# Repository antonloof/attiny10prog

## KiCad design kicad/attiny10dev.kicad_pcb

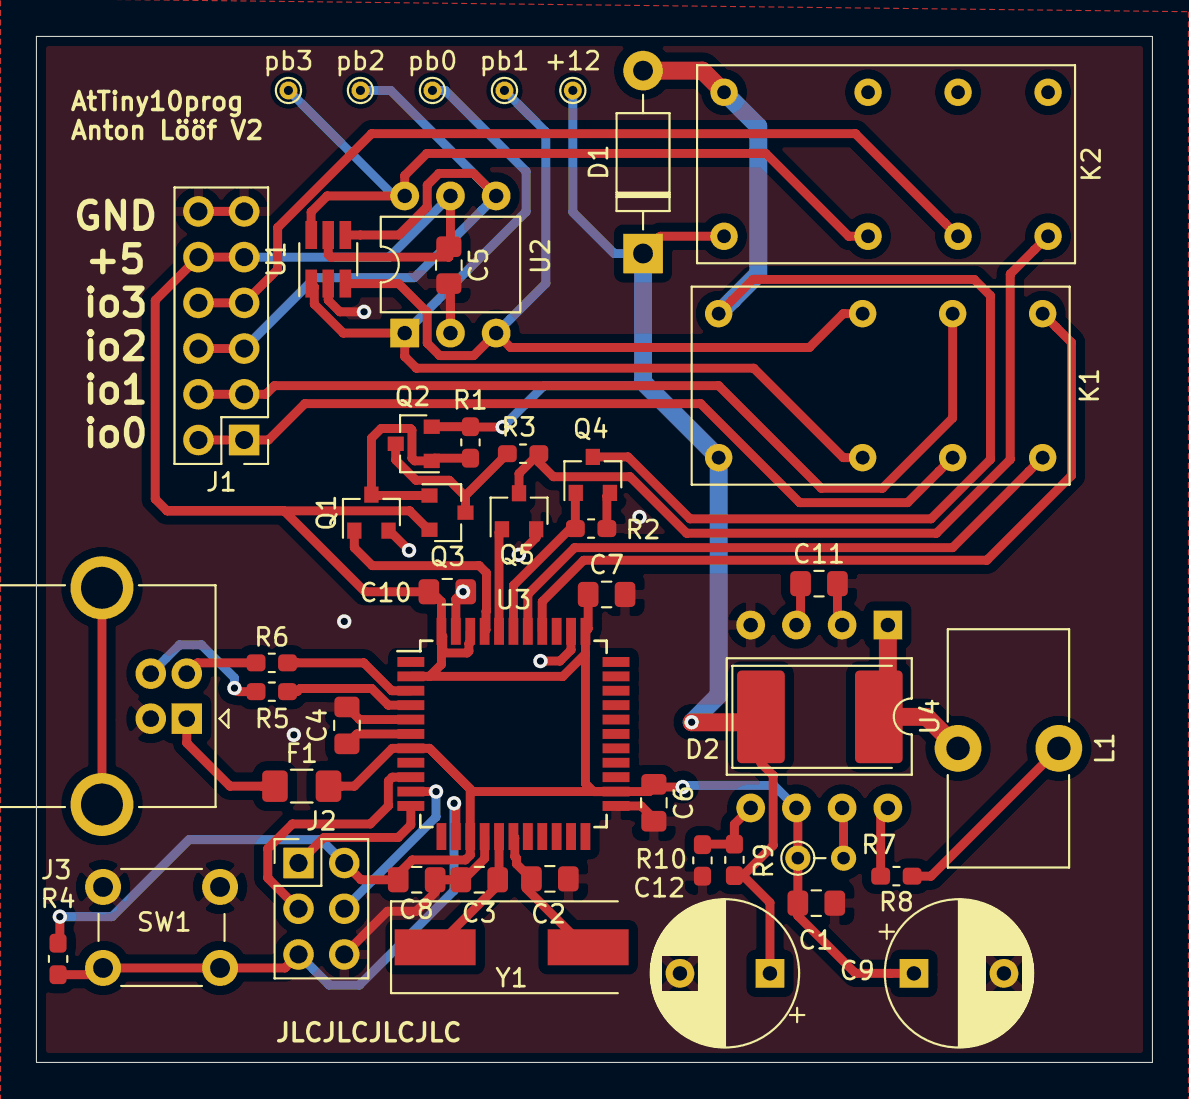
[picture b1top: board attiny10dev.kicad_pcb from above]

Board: 2 copper layers, 62.0 x 57.0 mm, 47 parts (0 on the bottom side), 37 nets.

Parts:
+12: TestPoint; TestPoint_THTPad_D1.0mm_Drill0.5mm
C1, C5, C6, C7, C8, C10: 100n; C_0805_2012Metric_Pad1.15x1.40mm_HandSolder
C2, C3: 22p; C_0805_2012Metric_Pad1.15x1.40mm_HandSolder
C4: 1u; C_0805_2012Metric_Pad1.15x1.40mm_HandSolder
C9, C12: 470u; CP_Radial_D8.0mm_P5.00mm
C11: 500p; C_0805_2012Metric_Pad1.15x1.40mm_HandSolder
D1: D; D_DO-41_SOD81_P10.16mm_Horizontal
D2: D; D_3220_8050Metric_Pad2.65x5.15mm_HandSolder
F1: 500ma; Fuse_1206_3216Metric_Pad1.42x1.75mm_HandSolder
J1: Conn_02x06_Odd_Even; PinHeader_2x06_P2.54mm_Vertical
J2: Conn_02x03_Odd_Even; PinHeader_2x03_P2.54mm_Vertical
J3: USB_B; USB_B_OST_USB-B1HSxx_Horizontal
K1, K2: m4-12h
L1: 33u; L_Toroid_Vertical_L13.0mm_W6.5mm_P5.60mm
Q1, Q3, Q4, Q5: 2N7002; SOT-23
Q2: BSS84; SOT-23
R1, R2, R3, R4, R10: 10k; C_0603_1608Metric_Pad1.05x0.95mm_HandSolder
R5, R6: 22; C_0603_1608Metric_Pad1.05x0.95mm_HandSolder
R7: 470m; R_Axial_DIN0204_L3.6mm_D1.6mm_P2.54mm_Vertical
R8: 180; C_0603_1608Metric_Pad1.05x0.95mm_HandSolder
R9: 86k; C_0603_1608Metric_Pad1.05x0.95mm_HandSolder
SW1: SW_Push; SW_PUSH_6mm
U1: ATtiny10-TS; SOT-23-6_Handsoldering
U2: ATtiny10-TS; DIP-6_W7.62mm
U3: ATmega32U4-AU; TQFP-44_10x10mm_P0.8mm
U4: MC34063AD; DIP-8_W10.16mm
Y1: 16Mhz; Crystal_SMD_HC49-SD
pb0, pb1, pb2, pb3: TestPoint; TestPoint_THTPad_D1.0mm_Drill0.5mm

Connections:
+5V: C1.1, C5.1, C6.1, C7.1, C8.1, C9.1, C10.1, F1.2, J1.9, J1.10, J2.2, Q3.2, R4.1, R7.1, U1.5, U2.5, U3.2, U3.7, U3.14, U3.24, U3.34, U3.42, U3.44, U4.6
+12V: +12.1, C12.1, D1.1, D2.1, K1.1, K2.1, Q2.2, R1.1, R9.1
/hard_reset: Q1.1, U3.41
/io0: J1.1, J1.2, K1.4
/io1: J1.3, J1.4, K1.7
/io2: J1.5, J1.6, U1.4, U2.4, pb2.1
/io3: J1.7, J1.8, K2.4
/lower_relay: D1.2, K1.10, K2.10, Q4.3
/pb0: K1.3, U1.1, U2.1, pb0.1
/pb1: K1.8, U1.3, U2.3, pb1.1
/pb3: K2.3, U1.6, U2.6, pb3.1
/prog: Q4.1, R2.1, U3.39
/prog_miso: J2.1, U3.11
/prog_mosi: J2.4, U3.10
/prog_rst: J2.5, R4.2, SW1.2, U3.13
/prog_sck: J2.3, U3.9
/reset_low: Q5.1, U3.40
/tpi_clk: K1.6, U3.37
/tpi_data: K1.5, U3.38
GND: C1.2, C2.2, C3.2, C4.2, C5.2, C6.2, C7.2, C8.2, C9.2, C10.2, C11.2, C12.2, J1.11, J1.12, J2.6, J3.4, Q1.2, Q4.2, Q5.2, R2.2, R10.2, SW1.1, U1.2, U2.2, U3.5, U3.15, U3.23, U3.35, U3.43, U4.2, U4.4
unnamed: C2.1, U3.17, Y1.2
unnamed: C3.1, U3.16, Y1.1
unnamed: C4.1, U3.6
unnamed: C11.1, U4.3
unnamed: D2.2, L1.2, U4.1
unnamed: F1.1, J3.1
unnamed: J3.2, R6.1
unnamed: J3.3, R5.1
unnamed: K2.5, Q5.3, R3.1
unnamed: L1.1, R8.1
unnamed: Q1.3, Q2.1, Q3.1, R1.2
unnamed: Q2.3, Q3.3, R3.2
unnamed: R5.2, U3.4
unnamed: R6.2, U3.3
unnamed: R7.2, U4.7
unnamed: R8.2, U4.8
unnamed: R9.2, R10.1, U4.5

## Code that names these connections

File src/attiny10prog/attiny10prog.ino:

#define RST_PIN A5
#define PROG_PIN A3
#define TPI_CLK_PIN A1
#define TPI_DATA_PIN A2
#define RST_LOW_PIN A4

#define OP_SKEY    0b11100000
#define OP_SLDCS   0b10000000
#define OP_SSTCS   0b11000000
#define OP_SIN     0b00010000
#define OP_SOUT    0b10010000
#define OP_SSTPR_L 0b01101000
#define OP_SSTPR_H 0b01101001
#define OP_SLD     0b00100000
#define OP_SST     0b01100000

const unsigned char NVM_KEY[] = {0x12, 0x89, 0xAB, 0x45, 0xCD, 0xD8, 0x88, 0xFF};

void tpi_try_enable(char reset) {
  digitalWrite(RST_PIN, reset);
  for (int i = 0; i < 16; i++) {
    tpi_send_bit(1);
  }
}

void tpi_send_bit(unsigned char c) {
  digitalWrite(TPI_CLK_PIN, 0);
  digitalWrite(TPI_DATA_PIN, c);
  digitalWrite(TPI_CLK_PIN, 1);
}

void tpi_clock_pulse() {
  digitalWrite(TPI_CLK_PIN, 0);
  digitalWrite(TPI_CLK_PIN, 1);
}

void tpi_send(unsigned char c) {
  digitalWrite(TPI_CLK_PIN, 0);
  tpi_send_bit(0);
  char parity = 0;
  for (int i = 0; i < 8; i++) {
    char nextbit = c & (1 << i) ? 1 : 0;
    parity ^= nextbit;
    tpi_send_bit(nextbit);
  }
  
  tpi_send_bit(parity);
  tpi_send_bit(1);
  tpi_send_bit(1);
  digitalWrite(TPI_CLK_PIN, 0);
  digitalWrite(TPI_DATA_PIN, 1);
}

unsigned char tpi_get() {
  pinMode(TPI_DATA_PIN, INPUT);
  tpi_clock_pulse();
  tpi_clock_pulse();
  tpi_clock_pulse();
  unsigned char out = 0; 
  unsigned char parity = 0;
  for (int i = 0; i < 8; i++) {
    tpi_clock_pulse();
    char c = digitalRead(TPI_DATA_PIN);
    parity ^= c;
    out |= (c << i);
  }
  tpi_clock_pulse();
  parity ^= digitalRead(TPI_DATA_PIN);
  tpi_clock_pulse();
  tpi_clock_pulse();
  pinMode(TPI_DATA_PIN, OUTPUT);
  return out;
}

void enable_nvm() {
  tpi_send(OP_SKEY);
  for (int i = 0; i < 8; i++) {
    tpi_send(NVM_KEY[7-i]);
  }
  tpi_send(OP_SLDCS | 0x0);
  if (tpi_get() != 2) {
    Serial.println("Failed to enable NVM programming");  
  }
}

char set_no_extra_get_stuff() {
  tpi_send(OP_SSTCS | 0x02);
  tpi_send(0x7);
  tpi_send(OP_SLDCS | 0x02);
  return tpi_get() == 0b111;
}

unsigned char serial_in_addr_to_op_code(unsigned char opcode, unsigned char addr) {
  return (opcode | ((addr & 0b110000) << 1)) | (addr & 0b1111);
}

unsigned char read_io(unsigned char addr) {
  tpi_send(serial_in_addr_to_op_code(OP_SIN, addr));
  return tpi_get();
}

void write_io(unsigned char addr, unsigned char val) {
  tpi_send(serial_in_addr_to_op_code(OP_SOUT, addr));
  tpi_send(val);
}

void pointer_load(unsigned int addr) {
  unsigned char high = addr >> 8;
  unsigned char low = addr & 0xFF;
  tpi_send(OP_SSTPR_L);
  tpi_send(low);
  tpi_send(OP_SSTPR_H);
  tpi_send(high);
}

unsigned char data_read(char inc) {
  tpi_send(OP_SLD | (inc ? 0b100 : 0));
  return tpi_get();
}

unsigned char data_write(char inc, unsigned char data) {
  tpi_send(OP_SST | (inc ? 0b100 : 0));
  tpi_send(data);
}

void set_rstdisbl(char val) {
  write_io(0x33, 0x14); // should erase next section we write to
  pointer_load(0x3F41);
  data_write(0, 0);
  wait_nvm_ready();
  if (val) {
    pointer_load(0x3F40);
    write_flash(0b11111110, 0xFF);
  }
}

volatile void wait_nvm_ready() {
  unsigned char res = 1;
  while (res) {
    res = read_io(0x32);
  }
}

void erase_chip() {
  write_io(0x33, 0x10); // should erase ship
  pointer_load(0x4001);
  data_write(0, 0);
  wait_nvm_ready();
}

void write_flash(unsigned char lower, unsigned char upper) {
  // does not load address, increments address +2
  // use pointer_load for that 
  write_io(0x33, 0x1D);
  data_write(1, lower);
  data_write(1, upper);
  wait_nvm_ready();
}


void start() {
  digitalWrite(TPI_DATA_PIN, 0);
  digitalWrite(PROG_PIN, 1);
  delay(100);
  
  tpi_try_enable(0);
  char ok = set_no_extra_get_stuff();
  if (!ok) {
    tpi_try_enable(1);
    ok = set_no_extra_get_stuff();
    if (!ok) {
      Serial.print("Failed to init tpi");
      return;
    }
  }
  enable_nvm();
  erase_chip();
  pointer_load(0x4000);
}

void finish() {
  tpi_send(OP_SSTCS | 0x0);
  tpi_send(0);
  delay(100);
  digitalWrite(PROG_PIN, 0);
  delay(100);
  digitalWrite(PROG_PIN, 1);
  delay(100);
  digitalWrite(PROG_PIN, 0);
}

void dump_mem() {
  pointer_load(0x4000);
  for (int i = 0; i < 1024; i++) {
    unsigned char c = data_read(1);
    if (c < 16) {
      Serial.print("0");
    }
    Serial.print(c, HEX);
  }
}

void setup() {
  pinMode(RST_PIN, OUTPUT);
  pinMode(PROG_PIN, OUTPUT);
  pinMode(TPI_CLK_PIN, OUTPUT);
  pinMode(TPI_DATA_PIN, OUTPUT);
  Serial.begin(115200);
}

unsigned char buf[4];
int i = 0;

unsigned char to_char(unsigned char c) {
  if (c <= '9') {
    return c - '0';
  }
  return 10 + c - 'A';
}

unsigned char to_byte(unsigned char c1, unsigned char c2) {
  return 16 * to_char(c1) + to_char(c2);
}

void loop() {
  if (Serial.available() > 0) {
    char com = Serial.read();
    Serial.write(com);
    
    if (com == 'S') {
      start();
      i = 0;
    } else if (com == 'V') {
      set_rstdisbl(1);
    } else if (com == 'v') {
      set_rstdisbl(0);
    } else if (com == 'X') {
      finish();
    } else if (com == 'R') {
      dump_mem();
      pointer_load(0x4000);
    } else {
      buf[i++] = com;
      if (i == 4) {
        write_flash(to_byte(buf[0], buf[1]), to_byte(buf[2], buf[3]));
        i = 0;
      }
    }
  }
}

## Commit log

2021-02-19 Add arguments
2021-02-21 add more debug#
2021-02-21 Create V2 of shematic
    with integrated boost and uC
2021-02-26 Add 12v reset
2021-02-28 Add 12v reset to script and properly to prog
2021-02-28 Work on next gen pcb
2021-03-01 V2 of pcb
2021-03-02 Finalize rev 2 pcb
2021-03-03 add jlc order no marker
2021-04-19 Fix boost
2021-04-21 Use correct ports, send 2 bytes at all times
